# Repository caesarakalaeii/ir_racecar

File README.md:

## ir_racecar
This repository is for a lane detection system on an MIT-RACEcar-style robot. Multiple approaches will be explored, one will be using infrared lights.

This project is now deprecated, and will no longer be maintained.

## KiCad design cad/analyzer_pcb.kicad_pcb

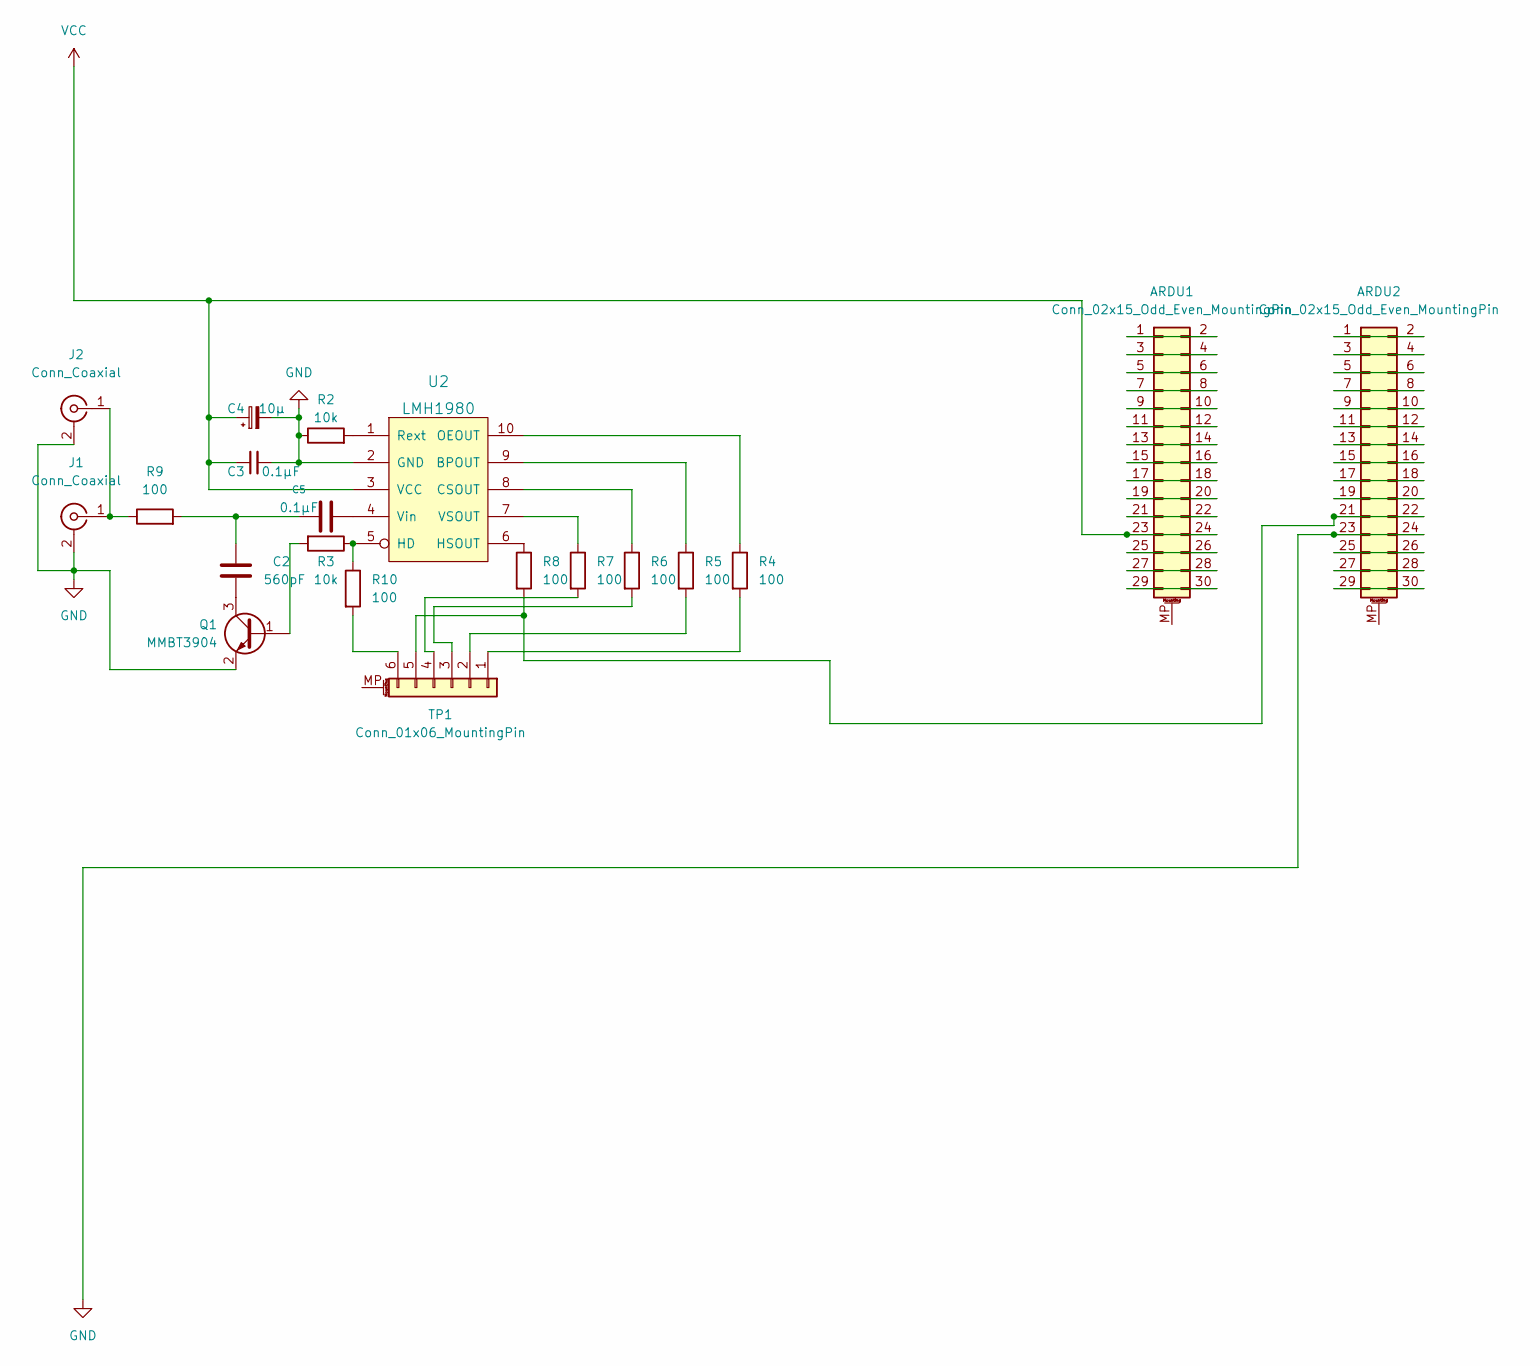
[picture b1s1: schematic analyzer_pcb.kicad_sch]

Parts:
ARDU1, ARDU2: Conn_02x15_Odd_Even_MountingPin; PinSocket_2x15_P2.54mm_Vertical
C2: 560pF; C_0805_2012Metric
C3, C5: 0.1µF; C_0805_2012Metric
C4: 10µ; C_1206_3216Metric
J1, J2: Conn_Coaxial; CUI_RCJ-041
Q1: MMBT3904; SOT-23
R2, R3: 10k; R_0805_2012Metric
R4, R5, R6, R7, R8, R9, R10: 100; R_0805_2012Metric
TP1: Conn_01x06_MountingPin; PinSocket_1x06_P2.54mm_Vertical
U2: LMH1980; VSSOP-10_3x3mm_P0.5mm

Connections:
GND: ARDU2.23, ARDU2.24, C3.2, C4.2, J1.2 (Ext), J2.2 (Ext), Q1.2 (E), R2.1, U2.2 (GND)
unnamed: ARDU1.1, ARDU1.2
unnamed: ARDU1.3, ARDU1.4
unnamed: ARDU1.5, ARDU1.6
unnamed: ARDU1.7, ARDU1.8
unnamed: ARDU1.9, ARDU1.10
unnamed: ARDU1.11, ARDU1.12
unnamed: ARDU1.13, ARDU1.14
unnamed: ARDU1.15, ARDU1.16
unnamed: ARDU1.17, ARDU1.18
unnamed: ARDU1.19, ARDU1.20
unnamed: ARDU1.21, ARDU1.22
unnamed: ARDU1.25, ARDU1.26
unnamed: ARDU1.27, ARDU1.28
unnamed: ARDU1.29, ARDU1.30
unnamed: ARDU2.1, ARDU2.2
unnamed: ARDU2.3, ARDU2.4
unnamed: ARDU2.5, ARDU2.6
unnamed: ARDU2.7, ARDU2.8
unnamed: ARDU2.9, ARDU2.10
unnamed: ARDU2.11, ARDU2.12
unnamed: ARDU2.13, ARDU2.14
unnamed: ARDU2.15, ARDU2.16
unnamed: ARDU2.17, ARDU2.18
unnamed: ARDU2.19, ARDU2.20
unnamed: ARDU2.21, ARDU2.22, R8.2, TP1.5
unnamed: ARDU2.25, ARDU2.26
unnamed: ARDU2.27, ARDU2.28
unnamed: ARDU2.29, ARDU2.30
unnamed: C2.1, C5.1, R9.2
unnamed: C2.2, Q1.3 (C)
unnamed: C5.2, U2.4 (Vin)
unnamed: J1.1 (In), J2.1 (In), R9.1
unnamed: Q1.1 (B), R3.2
unnamed: R2.2, U2.1 (Rext)
unnamed: R4.1, U2.10 (OEOUT)
unnamed: R4.2, TP1.1
unnamed: R5.1, U2.9 (BPOUT)
unnamed: R5.2, TP1.2
unnamed: R6.1, U2.8 (CSOUT)
unnamed: R7.1, U2.7 (VSOUT)
unnamed: R8.1, U2.6 (HSOUT)
unnamed: R3.1, R10.1, U2.5 (HD)
unnamed: R10.2, TP1.6
unnamed: R6.2, TP1.3
unnamed: R7.2, TP1.4
VCC: ARDU1.23, ARDU1.24, C3.1, C4.1, U2.3 (VCC)

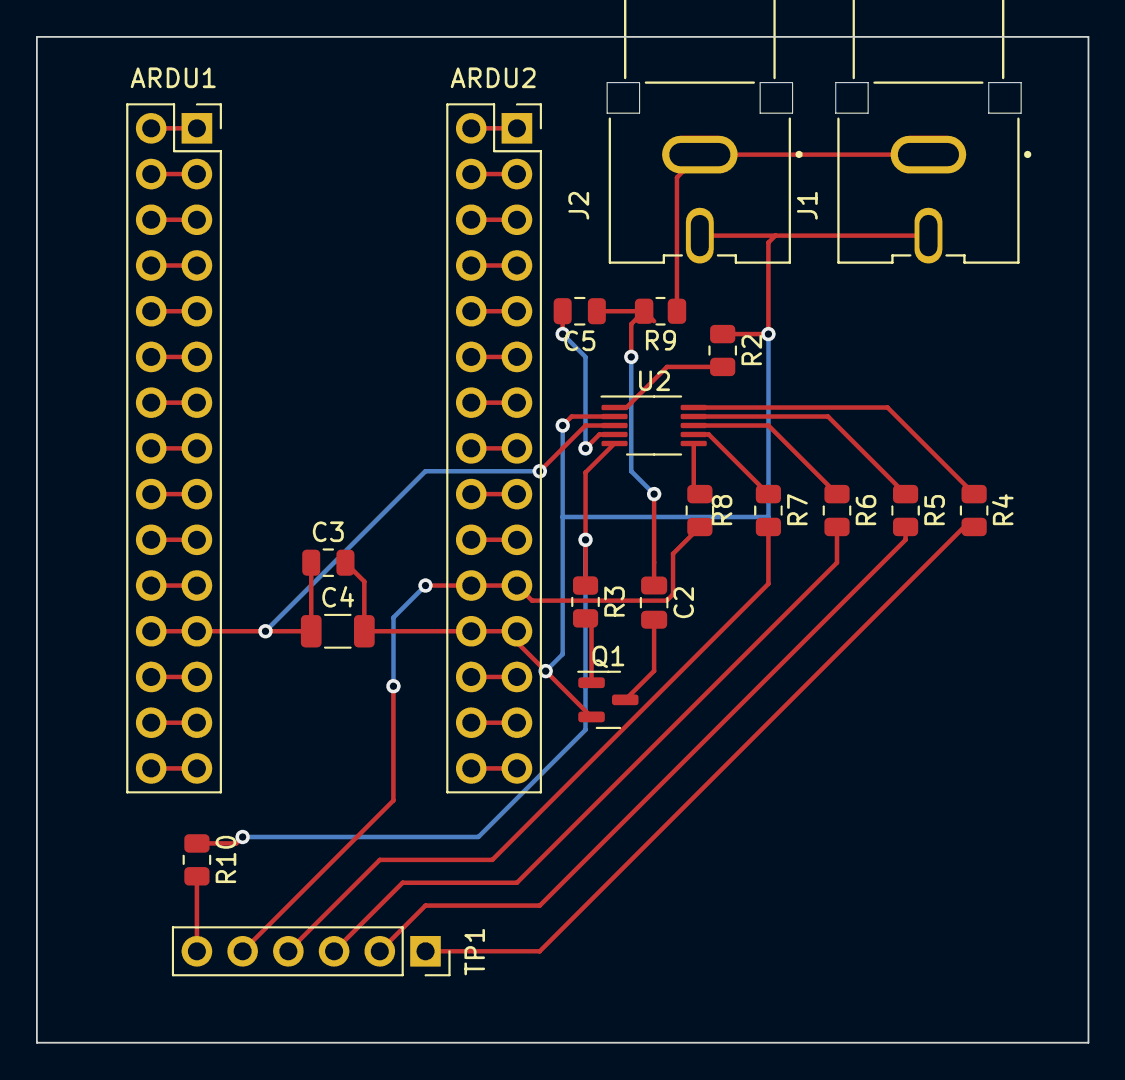
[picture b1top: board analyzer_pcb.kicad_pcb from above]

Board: 2 copper layers, 58.4 x 55.9 mm, 20 parts (0 on the bottom side), 47 nets.

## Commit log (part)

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2022-12-07 added docu for pwmgen
2022-12-07 added pwm_Sync
    Arduino script to generate a PWM signal, change it with serial inputs and using interrupts so toggle it
2022-12-07 uploaded toSerialApp
    simple tkinter application to send frequency and duty Cycle to arduino
2022-12-07 added docu for toSerialAPP
2022-12-07 added TODOs
2022-12-07 adden newlines
2022-12-07 fixing typos
2022-12-07 more typos
2022-12-14 added more programs
    added cli serial interface and openCV test program with multiple Cam views
2022-12-14 reformattet repository, added more files
2022-12-14 now really added folders
2022-12-14 added script to show fps
2022-12-14 added script to show current fps
2022-12-15 updated lmh1980 pcb
2022-12-15 added some info for CAD files
2022-12-15 added more views, some decluttering
2022-12-15 reworking to accomodate GUI, currently not functional
2022-12-16 added old Versions wich still works
2023-02-07 Added first calibration from ROS, minor changes
2023-02-09 new calibration data
2023-02-14 added publishing script
2023-02-17 refactored to allow catkin compatability
2023-03-14 test script to merge two images for a panorama view
2023-04-05 more scripts for different approaches
2023-04-05 Added "dumb" feature to stich two images together removed bugs
2023-04-11 added variable for better readability
2023-04-18 Refactored for better usability
2023-04-18 added vscode to ignore
2023-04-24 added cad files for cam fixtures
2023-04-24 Added more infos, Links, updated todos
2023-04-24 added new lines
2023-04-24 more new lines
2023-04-28 added file to test cameras without ROS
2023-04-28 added functionality for ROS launch, improved runtime
2023-05-02 more ignore
2023-05-02 added rospy logging
2023-05-02 removed bug in logging
2023-05-02 added direct import function, removed logging
2023-05-02 readded verbosity option
2023-05-02 added functionality to support **kwargs
2023-05-02 fixing stuff
2023-05-02 fixed more stuff
2023-05-02 further improved runtime
2023-05-02 More debug options
2023-05-02 some more error handeling
2023-05-03 more logging, currently not able to be started from roslaunch
2023-05-03 fixed error whith importing parameters
2023-05-04 trying to add cuda functioality
2023-05-04 refactored some stuff
2023-05-04 made cuda device variable
2023-05-04 added compatibility for older opencv versions
2023-05-04 more debug infos
2023-05-04 now actually made functional with older versions
2023-05-04 more error handling
2023-06-04 test for refactoring
2023-06-04 tests for refactoring, nonfunctional
2023-06-04 Refactor paramaters to nested dictionary
2023-06-04 renamed file
2023-06-04 commented and changed default values
2023-06-04 error in line 433 might be image conditions
2023-06-05 after some time it might try to allocate 122GB, also still not working
2023-06-05 Working, very slow, relocate some stuff to init
2023-06-05 Jointype 2 seems to use CUDA, warning and comments added
2023-06-05 prepared for refactor to universal logger
2023-06-05 started work
2023-06-05 Changing 'print' to 'logger'
2023-06-05 Changing print to logger
2023-06-05 added support for file logging
2023-06-05 More logging
2023-06-06 made finder variable, decluttering
2023-06-30 added comment
2023-07-17 fixed pwm gen added diff with variable threshhold
2023-07-19 stuff
2023-07-19 made fps show in ROS
2023-07-19 hopefully made it work again
2023-07-19 more fixing
2023-07-19 fixing
2023-07-19 fixerino
2023-07-19 more verbosity
2023-07-19 more sability to test
2023-07-20 more bug fixing
2023-07-20 test
2023-07-20 more testing
2023-07-20 testing
2023-07-20 trying cuda matcher
2023-07-24 added cuda functionality, experimental
2023-07-25 some fixing
2023-07-25 hard coded b/w images
2023-07-25 switched encoding to mono8
2023-07-25 changed encogin on recieving end
2023-07-25 fixed typo
2023-07-25 undid everyting again
2023-07-25 more testing, funcionality restored
2023-07-25 added todo
2023-08-02 added timing prints for cuda
2023-08-02 fixed error
2023-08-02 fixed wrong logging
2023-08-02 added complete timer
2023-08-02 changed stuff
2023-08-02 more timing
2023-08-02 more stuff
2023-08-02 changed values
2023-08-02 trying stuff
2023-08-02 more cuda
2023-08-02 trying to debug
2023-08-02 removing error handling
2023-08-02 added test_cuda.py from opencv_samples
2023-08-02 added tests_common from opencv samples
2023-08-02 mroe testing
2023-08-02 mooooore testing
2023-08-03 more trying
2023-08-03 more trying, last commit works
2023-08-03 more trying, last commit worked, but abyssmal perf
2023-08-03 better formatting
2023-08-03 rolled back
2023-08-03 testing using cupy
2023-08-03 testing, cuda non functional
2023-08-03 ignoring cupy errors
2023-08-03 ignoring everything
2023-08-03 moretests
2023-08-03 undid cupy
2023-08-03 tset
2023-08-04 removed cropping
2023-11-02 added timings
2023-11-02 refactor for older python vers
2023-11-03 now with timing
